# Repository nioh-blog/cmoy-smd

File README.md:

# cmoy-smd
# KiCad (22-Jun-2014BZR 4027)-stable on: Raspberry PI 2B && linux deploy linux jessy
# ..::NIOH::..
# license: https://www.gnu.org/licenses/gpl.html

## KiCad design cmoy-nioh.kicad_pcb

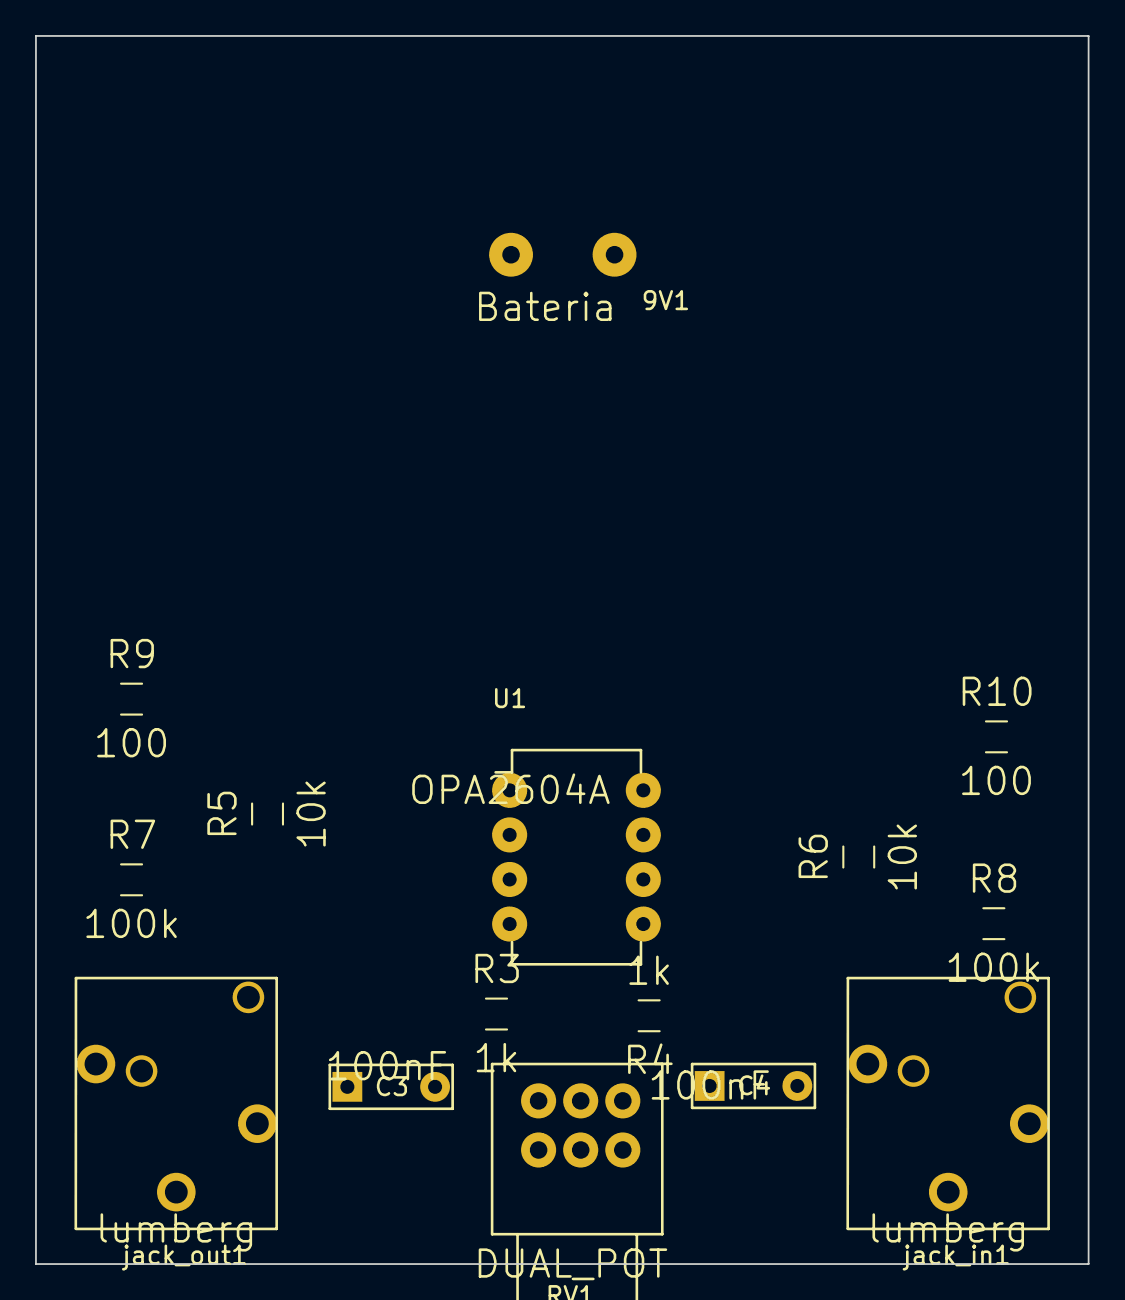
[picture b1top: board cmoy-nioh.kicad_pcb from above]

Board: 2 copper layers, 60.0 x 70.0 mm, 15 parts (0 on the bottom side), 15 nets, no tracks yet.

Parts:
9V1: Bateria; tk_SolderWirePad_2x_1mmDrill-nioh
C3, C4: 100nF; tk_wima_C_Rect_L7_W2.5_P5
R3, R4: 1k; tk_SMD_HandSold_805_R
R5, R6: 10k; tk_SMD_HandSold_805_R
R7, R8: 100k; tk_SMD_HandSold_805_R
R9, R10: 100; tk_SMD_HandSold_805_R
RV1: DUAL_POT; tk_Potentiometer_10k-double-nioh
U1: OPA2604A; tk_DIP-8_W7.62mm
jack_in1: lumberg; tk_lumberg
jack_out1: lumberg; tk_lumberg

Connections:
GNDREF: R3.2, R4.2, R7.1, R8.2, RV1.1, RV1.4, jack_in1.1, jack_out1.1
unnamed: R10.1, jack_out1.3
unnamed: R4.1, R6.1, U1.6
unnamed: R3.1, R5.1, U1.2
unnamed: C4.1, RV1.5
unnamed: C3.2, R7.2, U1.3
unnamed: C3.1, RV1.2
unnamed: RV1.6, jack_in1.3
unnamed: RV1.3, jack_in1.2
unnamed: C4.2, R8.1, U1.5
unnamed: R9.1, jack_out1.2
unnamed: R6.2, R10.2, U1.7
unnamed: R5.2, R9.2, U1.1
VCC: 9V1.1, U1.8
VEE: 9V1.2, U1.4

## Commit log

2017-08-25 new files
2017-08-25 25.08.2017
2017-08-25 z androida
2017-08-29 deleted some files
2017-08-30 reorg.
2017-08-30 dalzmian
2017-08-31 soic8
